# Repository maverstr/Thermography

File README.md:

# Thermography

Note : TFT_eSPI library should be moved into "Arduino/libraries" folder in root

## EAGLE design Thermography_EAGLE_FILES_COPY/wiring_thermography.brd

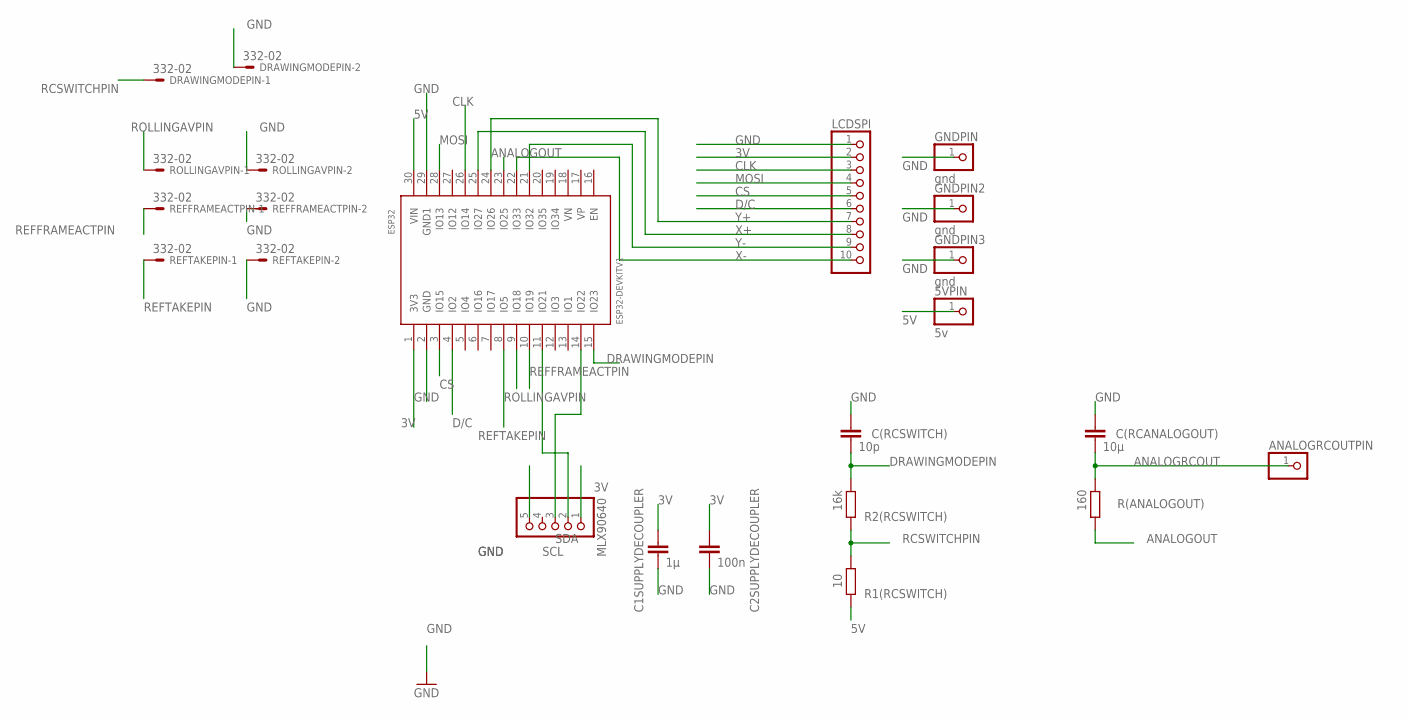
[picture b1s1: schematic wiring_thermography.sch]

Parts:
5VPIN: 5v; 1X01
ANALOGRCOUTPIN: PINHD-1X1; 1X01
C1SUPPLYDECOUPLER: 1µ; C5B5
C2SUPPLYDECOUPLER: 100n; C5B5
C(RCANALOGOUT): 10µ; C5B5
C(RCSWITCH): 10p; C5B5
DRAWINGMODEPIN: 332-02
ESP32: ESP32DEVKITV1; ESP32-DEVKITV1
GNDPIN, GNDPIN2, GNDPIN3: gnd; 1X01
LCDSPI: PINHD-1X10; 1X10
MLX90640: PINHD-1X5; 1X05
R1(RCSWITCH): 10; 0207/7
R2(RCSWITCH): 16k; 0207/7
R(ANALOGOUT): 160; 0207/7
REFFRAMEACTPIN: 332-02
REFTAKEPIN: 332-02
ROLLINGAVPIN: 332-02

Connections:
3V: C1SUPPLYDECOUPLER.1, C2SUPPLYDECOUPLER.1, ESP32.1 (3V3), LCDSPI.2, MLX90640.1
5V: 5VPIN.1, ESP32.30 (VIN), R1(RCSWITCH).1
ANALOGOUT: ESP32.23 (IO25), R(ANALOGOUT).1
ANALOGRCOUT: ANALOGRCOUTPIN.1, C(RCANALOGOUT).2, R(ANALOGOUT).2
CLK: ESP32.26 (IO14), LCDSPI.3
CS: ESP32.3 (IO15), LCDSPI.5
D/C: ESP32.4 (IO2), LCDSPI.6
DRAWINGMODEPIN: C(RCSWITCH).2, ESP32.15 (IO23), R2(RCSWITCH).2
GND: C1SUPPLYDECOUPLER.2, C2SUPPLYDECOUPLER.2, C(RCANALOGOUT).1, C(RCSWITCH).1, DRAWINGMODEPIN.2, ESP32.2 (GND), ESP32.29 (GND1), GNDPIN.1, GNDPIN2.1, GNDPIN3.1, LCDSPI.1, MLX90640.5, REFFRAMEACTPIN.2, REFTAKEPIN.2, ROLLINGAVPIN.2
MOSI: ESP32.28 (IO13), LCDSPI.4
RCSWITCHPIN: DRAWINGMODEPIN.1, R1(RCSWITCH).2, R2(RCSWITCH).1
REFFRAMEACTPIN: ESP32.10 (IO19), REFFRAMEACTPIN.1
REFTAKEPIN: ESP32.8 (IO5), REFTAKEPIN.1
ROLLINGAVPIN: ESP32.9 (IO18), ROLLINGAVPIN.1
SCL: ESP32.14 (IO22), MLX90640.3
SDA: ESP32.11 (IO21), MLX90640.2
X+: ESP32.25 (IO27), LCDSPI.8
X-: ESP32.22 (IO33), LCDSPI.10
Y+: ESP32.24 (IO26), LCDSPI.7
Y-: ESP32.21 (IO32), LCDSPI.9

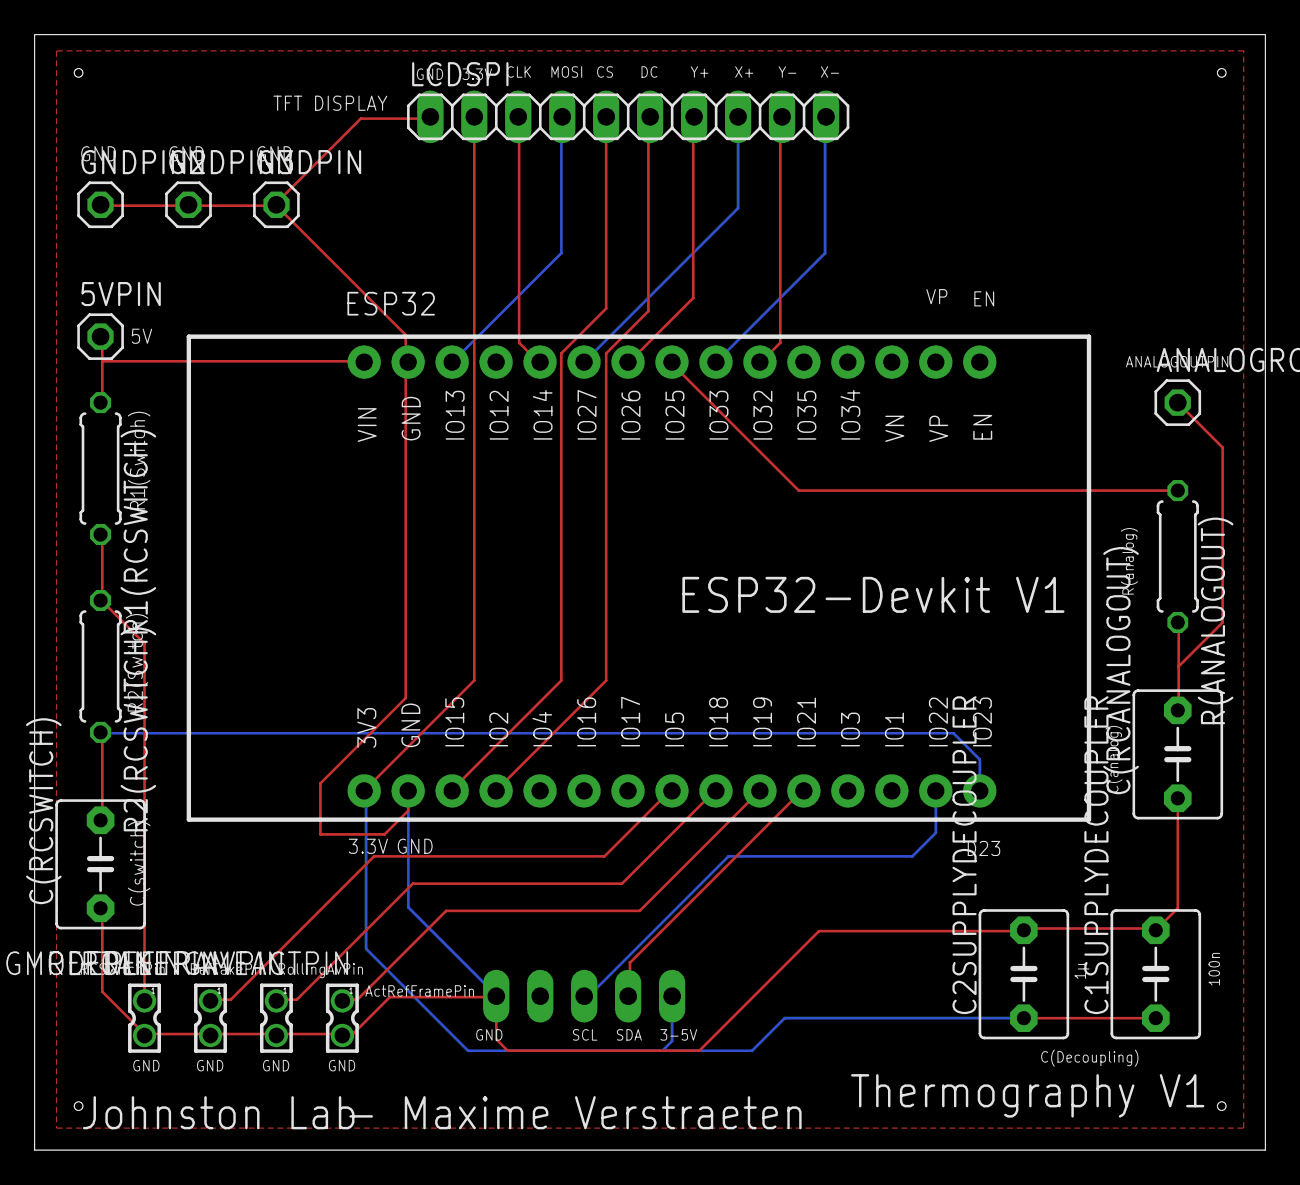
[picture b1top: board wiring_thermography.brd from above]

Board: 2 copper layers, 71.1 x 64.4 mm, 19 parts (1 on the bottom side), 20 nets.

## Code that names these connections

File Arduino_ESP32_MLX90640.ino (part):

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TSPoint p;

//switch
const int drawingModePin = 23;

//Pushbuttons
const int RollingAvPin = 18;
const int refFrameActivatePin = 19;
const int refTakePin = 5;
uint32_t pressedTimeStamp;
const uint32_t debounceDelay = 500;
bool flagCropIncrease = false;
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
void setup()
{
  flagDrawingMode = digitalRead(drawingModePin);
  dac_output_enable(DAC_CHANNEL_1); //enable analog output
  pressedTimeStamp = millis();
  Serial.begin(500000);
  Wire.begin();
  Wire.setClock(400000); //Increase I2C clock speed to 400kHz
  analogReadResolution(10); //required for touchscreen
  pinMode(RollingAvPin, INPUT_PULLUP);
  pinMode(refFrameActivatePin, INPUT_PULLUP);
  pinMode(refTakePin, INPUT_PULLUP);
  pinMode(drawingModePin, INPUT);
  attachInterrupt(digitalPinToInterrupt(refFrameActivatePin), setRefFrameActivateFlag, FALLING);
  attachInterrupt(digitalPinToInterrupt(RollingAvPin), setRollingAvFlag, FALLING);
  attachInterrupt(digitalPinToInterrupt(refTakePin), setRefFrameTakeFlag, FALLING);
  attachInterrupt(digitalPinToInterrupt(drawingModePin), interruptChangeCroppingMode, RISING);
  while (!Serial); //Wait for user to open terminal
  Serial.println("MLX90640 IR Array Example");
  if (isConnected() == false)
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  }

  if (flagChangeCroppingMode) {
    if (digitalRead(drawingModePin)) {
      setCroppingInteger(0, 320, 0, 240); //Resets to full view
      flagDrawingMode = true;

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
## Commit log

2019-08-06 upload on git
2019-08-06 folder
2019-08-06 folder rename
2019-08-06 added Processing and graphic test
2019-08-06 changed rolling to 4 and use bitwise operator
2019-08-06 optimization + compiler code
2019-08-06 updating reference frame with regards to calibration data
2019-08-07 added esp register manipulation for clock driving
2019-08-07 automatic calibration rm + reference frame over 16 frames
2019-08-07 corrected calibration
2019-08-07 corrected calibration scaling
2019-08-07 squeezing raw reading as values are now mapped
2019-08-07 implemented basis running std
2019-08-07 implemented basic running std
2019-08-07 added conditions on analog out for high std
2019-08-07 adding new class for running std
2019-08-08 update 08/08/19, working std
2019-08-15 added std controls
2019-08-15 updates vdd and ta on calibration
2019-08-16 calibration improved + std bug fixed
2019-08-16 added histogram equalization
2019-08-16 add processing real time histogram
2019-08-19 backup working 1908
2019-08-21 added waiting for new data
2019-08-22 corrected waiting for new data
2019-08-22 drawing functions reworked
2019-08-22 OK 2208 noon
2019-08-22 int(d/dt) + int opti
2019-08-22 cleanup
2019-08-22 additional cleanup
2019-08-23 fixed calibration
2019-08-23 rolling 2 frames + more precise framerate
2019-08-23 2309
2019-09-03 added mlx90614
2019-09-06 added python script visualisation
2019-09-09 added library
2019-09-13 added doc submodule
2019-09-16 added lib
2019-09-16 added eagle files
2019-09-16 added doc pdf
2019-09-17 added eeprom storage of values + reference frame taken on full frame whatever the cropping
2019-09-17 typo + added no viz text
2019-09-18 updated python viz to adapt to multiple crops
2019-09-18 typo
2019-09-19 added analog output viz
2019-09-19 changed wait for condition to keyboard press
2019-09-20 viz now implements lasso ROI
2019-09-22 2209 all
2019-09-25 added bill of mats
2019-09-25 updated eagle
2019-09-25 updated eagle files
2019-10-01 release
